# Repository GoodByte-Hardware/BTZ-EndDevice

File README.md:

<h1 align="center">BLE/Thread/Zigbee EndDevice</h1>

<p align="center">
  Low-power wireless sensor board based on the nRF54L15 for BLE Mesh, Thread/Matter and Zigbee
</p>

<p align="center" width="100%">

</p>

***

## ABOUT

BTZ-EndDevice is a battery-powered sensor node designed by GoodByte to compare BLE Mesh, Thread/Matter and Zigbee
on the same hardware.

<p align="center">
  
&nbsp; &nbsp; &nbsp; &nbsp;
  
</p>

***

## SPECIFICATIONS

| Parameter | Value |
| --- | --- |
| SoC | Nordic nRF54L15  |
| Sensors | STS4x (temperature), LTR-329ALS-01 (light), BMI270 (IMU), switchable power |
| Power | CR2032 coin cell or external supply, jumper JP1 for current measurement |
| Interfaces | SWD, GPIO headers, NFC antenna connector, button, LED |
| PCB | 35.0 × 35.0 mm, 4 layers |

***

## DESIGN FILES

All files below are generated by KiBot in CI.

| File | Description |
| --- | --- |
| [Schematic](Schematic/BTZ-EndDevice-schematic.pdf) | Full schematic (PDF) |
| [BOM (CSV)](Manufacturing/Assembly/BTZ-EndDevice-bom.csv) · [BOM (HTML)](Manufacturing/Assembly/BTZ-EndDevice-bom.html) | Bill of materials |
| [Interactive BOM](Manufacturing/Assembly/BTZ-EndDevice-ibom.html) | Component placement viewer (download and open in a browser) |
| [Pick and place](Manufacturing/Assembly/BTZ-EndDevice-CPL.csv) | Component positions for assembly |
| [Assembly drawing](Manufacturing/Assembly/BTZ-EndDevice-assembly.pdf) | Assembly drawing (PDF) |
| [Gerbers](Manufacturing/Fabrication/BTZ-EndDevice-GERBERS.zip) | Fabrication files (ZIP) |
| [Fabrication drawing](Manufacturing/Fabrication/BTZ-EndDevice-fabrication.pdf) | Stackup, drill and fabrication notes (PDF) |
| [3D model](3D/BTZ-EndDevice.step) | Board model (STEP) |
| [Test points](Testing/Testpoints/BTZ-EndDevice-testpoints.csv) | Test point positions and nets (CSV) |

***

## DIRECTORY STRUCTURE

    .
    ├─ 3D                 # STEP model of the board
    ├─ HTML               # Generated web page with all outputs
    ├─ Images             # Renders
    │
    ├─ kibot_resources    # External resources for KiBot
    │  ├─ colors          # Color theme for KiCad
    │  ├─ fonts           # Fonts used in the project
    │  ├─ scripts         # External scripts used with KiBot
    │  └─ templates       # Templates for KiBot generated reports
    │
    ├─ kibot_yaml         # KiBot YAML config files
    ├─ KiRI               # KiRI (visual schematic and PCB diff between revisions)
    │
    ├─ Library            # KiCad footprint and symbol libraries
    │  ├─ 3D Model        # Component 3D models
    │  ├─ Footprint       # Footprint libraries
    │  └─ Symbol          # Symbol libraries
    │
    ├─ Logos              # Logos
    │
    ├─ Manufacturing      # Assembly and fabrication documents
    │  ├─ Assembly        # Assembly documents (BOM, pick and place, notes)
    │  └─ Fabrication     # Fabrication documents (Gerbers, drill tables, notes)
    │
    ├─ Schematic          # Schematic PDF
    ├─ Templates          # Title block templates
    └─ Testing
       └─ Testpoints      # Test point tables

***

## LICENSE

This project is licensed under the MIT License, see [LICENSE](LICENSE).

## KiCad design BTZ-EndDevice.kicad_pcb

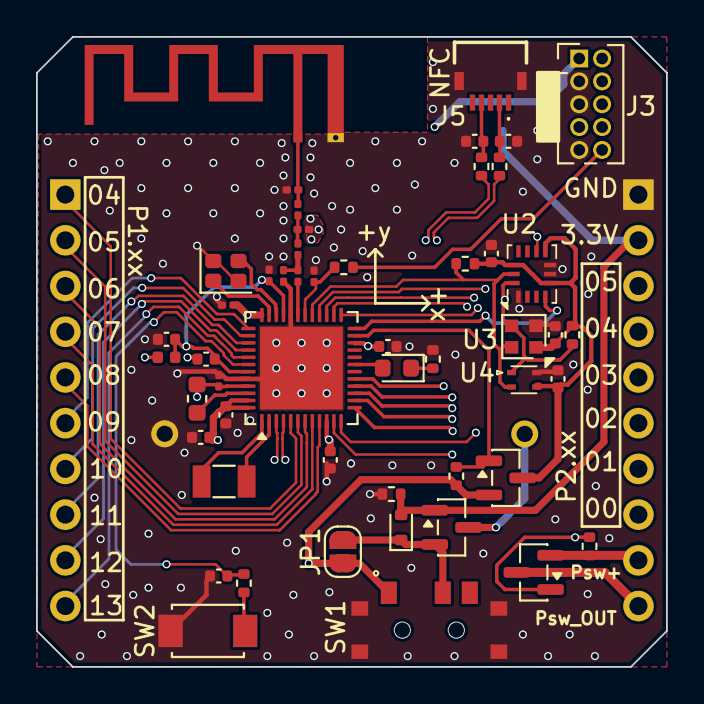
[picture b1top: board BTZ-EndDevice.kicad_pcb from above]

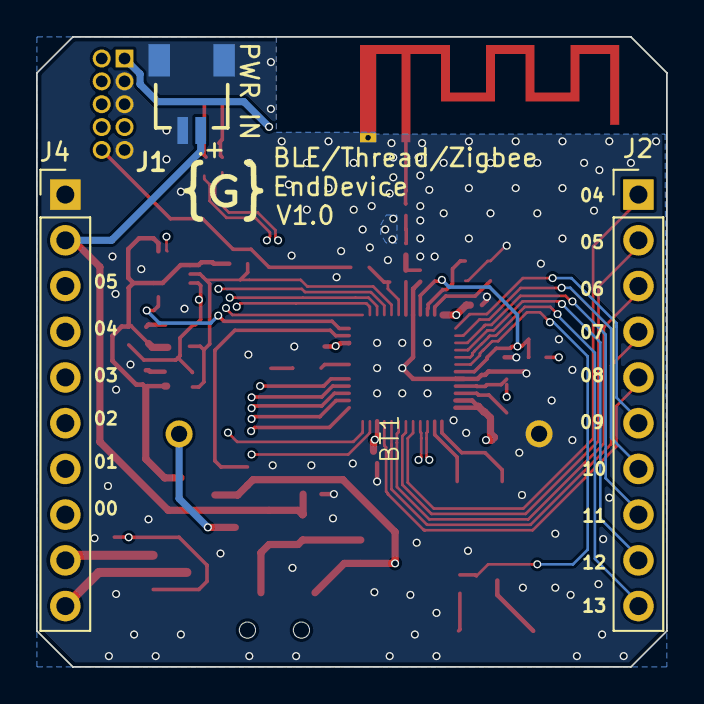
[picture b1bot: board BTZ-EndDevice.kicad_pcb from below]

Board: 4 copper layers, 35.0 x 35.0 mm, 55 parts (4 on the bottom side), 53 nets.

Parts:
AE1: Antenna; Texas_SWRA117D_2.4GHz_Left
BT1: CR2032; CR2032holder
C1: 10μF; C_0402_1005Metric
C2, C3, C5, C13, C15, C16: 100nF; C_0402_1005Metric
C4: 100nF; C_0201_0603Metric
C6: 2,2nF; C_0201_0603Metric
C7, C18: 10nF; C_0402_1005Metric
C8: 2,2μF; C_0402_1005Metric
C9: 2,2μF; C_0201_0603Metric
C10: 1,5pF; C_0201_0603Metric
C11: 2pF; C_0201_0603Metric
C12: 0.3pF; C_0201_0603Metric
C14: 3,9pF; C_0201_0603Metric
C17, C19: 300pF; C_0402_1005Metric
D1: D_Schottky; D_SOD-523
D2: LED; LED_0603_1608Metric
FB1: 120R@100MHz; L_0402_1005Metric
J1: Conn_01x02_MountingPin; 2035580207
J2, J4: Conn_01x10_Pin; PinHeader_1x10_P2.54mm_Vertical
J3: Conn_ARM_JTAG_SWD_10; PinHeader_2x05_P1.27mm_Vertical
J5: Conn_01x05_MountingPin; 59453051110ECHLF
JP1: SolderJumper_2_Open; SolderJumper-2_P1.3mm_Open_RoundedPad1.0x1.5mm
L1: 4,7μH; L_0603_1608Metric
L2: 2,7nH; L_0201_0603Metric
L3, L4: 3,5nH; L_0201_0603Metric
Q1, Q2, Q3: AO3401A; SOT-23
R1, R7: 470k; R_0402_1005Metric
R2: 1M; R_0402_1005Metric
R3: 3,3k; R_0402_1005Metric
R4, R5: 10k; R_0402_1005Metric
R6, R9: 1k; R_0402_1005Metric
R8, R10: 0R; R_0402_1005Metric
SW1: SW_SPDT; SSSS810701
SW2: SW_SPST; SW_TS-1088-AR02016
U1: nRF54L15-QFXX; QFN-48-1EP_6x6mm_P0.4mm_EP4.6x4.6mm
U2: BMI270; Bosch_LGA-14_3x2.5mm_P0.5mm
U3: STS4X
U4: LTR-329ALS-01; Lite-On_LTR-329ALS-01
Y1: 32MHz; Crystal_SMD_2016-4Pin_2.0x1.6mm
Y2: 32.768kHz; Crystal_SMD_3215-2Pin_3.2x1.5mm

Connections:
+3.3V: D1.2 (A), J1.1, J4.2, Q1.1 (G), R1.2
/Project Architecture/Section A - Title A/ANT: AE1.1 (A), C12.2, L4.2
/Project Architecture/Section A - Title A/BMI_INT1: U1.24 (P0.01), U2.4 (INT1)
/Project Architecture/Section A - Title A/BMI_INT2: U1.27 (P0.02), U2.9 (INT2)
/Project Architecture/Section A - Title A/DCC: L1.1, U1.46 (DCC)
/Project Architecture/Section A - Title A/DECD: C9.1, FB1.1, L1.2, U1.45 (DECD)
/Project Architecture/Section A - Title A/DECRF: C6.1, C7.1, C8.1, FB1.2, U1.33 (DECRF), U1.43 (DECA)
/Project Architecture/Section A - Title A/NFC+: R8.1, U1.3 (P1.02)
/Project Architecture/Section A - Title A/NFC-: R10.1, U1.4 (P1.03)
/Project Architecture/Section A - Title A/P1.04: J2.1, U1.5 (P1.04)
/Project Architecture/Section A - Title A/P1.05: J2.2, U1.6 (P1.05)
/Project Architecture/Section A - Title A/P1.06: J2.3, U1.7 (P1.06)
/Project Architecture/Section A - Title A/P1.07: J2.4, U1.8 (P1.07)
/Project Architecture/Section A - Title A/P1.08: J2.5, U1.9 (P1.08)
/Project Architecture/Section A - Title A/P1.09: J2.6, U1.37 (P1.09)
/Project Architecture/Section A - Title A/P1.10: J2.7, U1.38 (P1.10)
/Project Architecture/Section A - Title A/P1.11: J2.8, U1.39 (P1.11)
/Project Architecture/Section A - Title A/P1.12: J2.9, U1.40 (P1.12)
/Project Architecture/Section A - Title A/P1.13: J2.10, U1.41 (P1.13)
/Project Architecture/Section A - Title A/P2.00: J4.8, U1.11 (P2.00)
/Project Architecture/Section A - Title A/P2.01: J4.7, U1.12 (P2.01)
/Project Architecture/Section A - Title A/P2.02: J4.6, U1.13 (P2.02)
/Project Architecture/Section A - Title A/P2.03: J4.5, U1.14 (P2.03)
/Project Architecture/Section A - Title A/P2.04: J4.4, U1.15 (P2.04)
/Project Architecture/Section A - Title A/P2.05: J4.3, U1.16 (P2.05)
/Project Architecture/Section A - Title A/PW_SW+: J4.9, Q3.2 (S), R7.1
/Project Architecture/Section A - Title A/PW_SW_OUT: J4.10, Q3.3 (D)
/Project Architecture/Section A - Title A/RF: L2.1, U1.31 (ANT)
/Project Architecture/Section A - Title A/RF': C10.2, L2.2, L3.1
/Project Architecture/Section A - Title A/RF'': C11.2, L3.2, L4.1
/Project Architecture/Section A - Title A/SCL: R4.1, U1.29 (P0.04), U2.13 (SCx), U3.2 (SCL), U4.4 (SCL)
/Project Architecture/Section A - Title A/SDA: R5.1, U1.28 (P0.03), U2.14 (SDx), U3.1 (SDA), U4.3 (SDA)
/Project Architecture/Section A - Title A/SWCLK: J3.4 (SWCLK/TCK), U1.26 (SWDCLK)
/Project Architecture/Section A - Title A/SWDIO: J3.2 (SWDIO/TMS), U1.25 (SWDIO)
/Project Architecture/Section A - Title A/USER_LED: D2.2 (A), U1.19 (P2.08)
/Project Architecture/Section A - Title A/USER_SW: C18.2, R9.2, U1.42 (P1.14)
/Project Architecture/Section A - Title A/VBat: BT1.1 (+), Q1.3 (D)
/Project Architecture/Section A - Title A/VDD': D1.1 (K), JP1.1 (A), Q1.2 (S), SW1.2 (B)
/Project Architecture/Section A - Title A/~PW_SW_EN: Q3.1 (G), R7.2, U1.17 (P2.06)
/Project Architecture/Section A - Title A/~RST_Conn: J3.10 (~RESET), R6.2
/Project Architecture/Section A - Title A/~RST: C14.1, R6.1, U1.30 (~RESET)
/Project Architecture/Section A - Title A/~VDD_susp_EN: Q2.1 (G), R2.1, U1.23 (P0.00)
GND: AE1.2, BT1.2 (-), C1.2, C2.2, C3.2, C4.2, C5.2, C6.2, C7.2, C8.2, C9.2, C10.1, C11.1, C12.1, C13.2, C14.2, C15.2, C16.2, C17.2, C18.1, C19.2, J1.2, J1.MP (MountPin), J3.3 (GND), J3.5 (GND), J3.9 (GNDDetect), J4.1, J5.MP (MountPin), R1.1, R3.1, SW1.MP (C), SW2.1 (A), U1.32 (VSS_PA), U1.44 (VSS), U1.49 (VSS), U2.1 (SDO), U2.6 (GNDIO), U2.7 (GND), U3.4 (VSS), U4.2 (GND), Y1.2, Y1.4
unnamed: D2.1 (K), R3.2
unnamed: C19.1, J5.2, R8.2
unnamed: C17.1, J5.4, R10.2
unnamed: R9.1, SW2.2 (B)
unnamed: U1.1 (P1.00), Y2.2
unnamed: U1.2 (P1.01), Y2.1
unnamed: U1.34 (XC1), Y1.3
unnamed: U1.35 (XC2), Y1.1
VDD: C1.1, C2.1, C3.1, C4.1, C5.1, J3.1 (VTref), JP1.2 (B), Q2.2 (S), R2.2, SW1.3 (C), U1.10 (VDD), U1.22 (VDD), U1.36 (VDD), U1.47 (VDD), U1.48 (VDD)
VDD_susp: C13.1, C15.1, C16.1, Q2.3 (D), R4.2, R5.2, U2.5 (VDDIO), U2.8 (VDD), U2.12 (CSB), U3.3 (VDD), U4.1 (VDD)

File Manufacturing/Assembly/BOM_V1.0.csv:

"Reference","Value","Footprint","LCSC"
"C4","100nF","Capacitor_SMD:C_0201_0603Metric","C76939"
"C6","2,2nF","Capacitor_SMD:C_0201_0603Metric","C161488"
"C9","2,2μF","Capacitor_SMD:C_0201_0603Metric","C335106"
"C10","1,5pF","Capacitor_SMD:C_0201_0603Metric","C88913"
"C11","2pF","Capacitor_SMD:C_0201_0603Metric","C668326"
"C12","0.3pF","Capacitor_SMD:C_0201_0603Metric","C3904589"
"C14","3,9pF","Capacitor_SMD:C_0201_0603Metric","C1852416"
"C1","10μF","Capacitor_SMD:C_0402_1005Metric","C15525"
"C2,C3,C5,C13,C15,C16","100nF","Capacitor_SMD:C_0402_1005Metric","C1525"
"C7,C18","10nF","Capacitor_SMD:C_0402_1005Metric","C15195"
"C8","2,2μF","Capacitor_SMD:C_0402_1005Metric","C12530"
"C17,C19","300pF","Capacitor_SMD:C_0402_1005Metric","C1534"
"J3","Conn_ARM_JTAG_SWD_10","Connector_PinHeader_1.27mm:PinHeader_2x05_P1.27mm_Vertical",""
"Y1","32MHz","Crystal:Crystal_SMD_2016-4Pin_2.0x1.6mm","C187794"
"Y2","32.768kHz","Crystal:Crystal_SMD_3215-2Pin_3.2x1.5mm","C32346"
"D1","D_Schottky","Diode_SMD:D_SOD-523","C7502714"
"L2","2,7nH","Inductor_SMD:L_0201_0603Metric","C7216765"
"L3,L4","3,5nH","Inductor_SMD:L_0201_0603Metric","C3911055"
"FB1","120R@100MHz","Inductor_SMD:L_0402_1005Metric","C85812"
"L1","4,7μH","Inductor_SMD:L_0603_1608Metric","C76799"
"D2","LED","LED_SMD:LED_0603_1608Metric","C965804"
"J1","Conn_01x02_MountingPin","Library:2035580207","C160402"
"J5","Conn_01x05_MountingPin","Library:59453051110ECHLF",""
"SW1","SW_SPDT","Library:SSSS810701","C97433"
"U3","STS4X","Library:STS4X","C41410764"
"SW2","SW_SPST","Library:SW_TS-1088-AR02016","C720477"
"U1","nRF54L15-QFXX","Package_DFN_QFN:QFN-48-1EP_6x6mm_P0.4mm_EP4.6x4.6mm",""
"U2","BMI270","Package_LGA:Bosch_LGA-14_3x2.5mm_P0.5mm","C2836813"
"Q1,Q2,Q3","AO3401A","Package_TO_SOT_SMD:SOT-23","C15127"
"R1,R7","470k","Resistor_SMD:R_0402_1005Metric","C25790"
"R2","1M","Resistor_SMD:R_0402_1005Metric","C26083"
"R3","3,3k","Resistor_SMD:R_0402_1005Metric","C25890"
"R4,R5","10k","Resistor_SMD:R_0402_1005Metric","C25744"
"R6,R9","1k","Resistor_SMD:R_0402_1005Metric","C11702"
"R8,R10","0R","Resistor_SMD:R_0402_1005Metric","C17168"
"U4","LTR-329ALS-01","Library:Lite-On_LTR-329ALS-01","C284894"

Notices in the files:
README.md:
License: MIT
